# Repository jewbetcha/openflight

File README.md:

<p align="center">

  DIY Golf Launch Monitor using the OPS243-A Doppler Radar.
</p>

<p align="center">

</p>

> [!WARNING]
> **This project is in active development.** Features may be incomplete, unstable, or change without notice. Contributions and bug reports are welcome!

## Overview

OpenFlight is an open-source golf launch monitor built around the OPS243-A
Doppler radar, with an optional TI IWR6843 angle radar.

### What It Measures

- **Ball Speed**: 15-200 mph range with ±0.5% accuracy (OPS243-A)
- **Club Speed**: Detected from pre-impact readings (OPS243-A)
- **Smash Factor**: Ball speed / club speed ratio
- **Launch Angle**: Measured by the IWR6843; estimated when no trusted radar angle is available
- **Club Path**: Experimental pre-impact estimate from the IWR6843
- **Spin Rate**: Experimental candidate from rolling-buffer I/Q; not used for carry by default
- **Carry Distance**: Ballistic model with explicit fallbacks for missing measurements

### Hardware at a Glance

| Component | What it does | ~Cost |
|-----------|-------------|-------|
| OPS243-A Radar | Ball speed, club speed, experimental spin | $249 |
| Raspberry Pi 5 | Runs everything | $130 |
| 7" Touchscreen | Shows shot data | $46 |
| SparkFun SEN-14262 | Impact sound trigger for shot capture | $18 |
| Power supply + accessories | | $27 |
| **Subtotal, no angle radar** | | **~$400** |
| TI IWR6843LEVM + cable | Launch angle, experimental club path | $156 |
| **Total with angle radar** | | **~$556** |
| K-LD7 (×2) + FTDI adapters | Launch angle + club path (**deprecated**) | $140 |

Without an angle radar you still get ball speed, club speed, smash factor,
experimental spin, and estimated carry. The angle radar adds measured launch
angle and experimental club path.

> **⚠️ The K-LD7 angle radars are deprecated.** The supported angle radar is now the **TI IWR6843**. Don't buy K-LD7s for a new build; their software support remains for existing builds only. See the [full parts list](docs/PARTS.md) for details and links.

> **The IWR6843 needs custom firmware** — the stock TI demo doesn't expose the raw radar cube OpenFlight needs. A validated prebuilt image ships in `firmware/releases/`, so flashing it doesn't require the TI toolchain. See the [IWR6843 Operator Guide](docs/iwr6843/README.md).

## Getting Started

### 1. Get the parts

See the **[Parts List](docs/PARTS.md)** for everything you need with purchase links.

### 2. Wire it up

Follow the **[Sound Trigger Wiring Guide](docs/sound-trigger-wiring.md)** to connect the SEN-14262 to the OPS243-A. The (deprecated) K-LD7 modules connect via USB — no wiring needed.

**Adding the IWR6843 angle radar?** The Pi cannot power both radars over USB, so
the OPS243 moves to the Pi's GPIO UART header while the TI board takes the USB
port. Do it in this order, validating each step before the next — doing both at
once makes any failure ambiguous:

1. **[Move the OPS243 from USB to the Pi GPIO UART](docs/ops243-uart-migration.md)** — rewire and confirm the OPS still triggers on its own.
2. **[IWR6843 Operator Guide](docs/iwr6843/README.md)** — wire, flash the firmware, mount, aim, and measure geometry.

If your OPS243-A has **WiFi**, you cannot use the GPIO UART — its WiFi module
already drives the radar's UART receive line. Use a separately powered USB hub
instead; see the operator guide's Option B.

### 3. Set up the Pi

Flash Raspberry Pi OS (64-bit), plug in the radars, then run the interactive setup:

```bash
git clone https://github.com/jewbetcha/openflight.git
cd openflight
./scripts/setup/setup.sh
```

The script installs everything and walks you through the one-time hardware
configuration (radar flash setup, legacy K-LD7 device naming, auto-start, and
optional cloud sync) with prompts. It's safe to re-run any time.
See the **[Raspberry Pi Setup Guide](docs/raspberry-pi-setup.md)** for
details and troubleshooting. Touchscreen installations can use the
**[Startup Splash Screen](docs/splash-screen.md)** guide to install a
terminal-free desktop launcher with immediate startup progress.

### 4. Hit balls

```bash
# Default: rolling buffer mode with sound trigger
scripts/start-kiosk.sh

# With the IWR6843 angle radar (OPS243 on the Pi GPIO UART).
# Geometry values are examples — measure your own; see the operator guide.
scripts/start-kiosk.sh --iwr6843 \
  --ops-port /dev/ttyAMA0 \
  --iwr6843-tee-m 1.372 --iwr6843-net-m 4.064 \
  --iwr6843-tilt-deg 5.5 --iwr6843-radar-height-m 0.229 \
  --iwr6843-ball-height-m 0.021

# With legacy K-LD7 hardware (measure the mount tilt first)
scripts/start-kiosk.sh --kld7 --kld7-mount-tilt <measured-degrees>

# Swing speed training (air swings / speed sticks, no sound trigger)
scripts/start-kiosk.sh --swing-speed

# Development mode (no hardware)
scripts/start-kiosk.sh --mock

# With Geekworm X1202/X1206 battery monitoring
scripts/start-kiosk.sh --battery geekworm
```

The IWR6843 example values are not universal. Measure the geometry from the
antenna center and follow the [operator guide](docs/iwr6843/README.md#measure-the-geometry);
wrong values bias the result instead of producing an obvious startup error.

Then open http://localhost:8080 or use the touchscreen. Footer tabs switch
between Live, Stats, Shots, Camera, Players, and Debug. Tap the footer logo for
units, theme, and language; the footer power icon opens shutdown confirmation.
On Live, tap a metric to pin it top-left while keeping all metrics visible. Use
the Replay action on camera-backed shots to open a touch-friendly slow-motion
impact clip. The MP4 is generated only when Replay is selected and is cached
beside the raw camera capture. For a TV or tablet, use
[TV Display Mode](#tv-display-mode).

### 5. Sync to the cloud (optional)

OpenFlight can push your sessions to the **FlightWeb** cloud so you can review
shots from any device. It's opt-in, and **raw radar data never leaves your
Pi** — only shot results and session metadata are uploaded (verify with
`openflight-cloud push --dry-run`).

`setup.sh` offers to enable this and link your Pi. To do it by hand:

```bash
openflight-cloud link       # pair this Pi (enter a short code in your browser)
openflight-cloud status     # linked? queued? parked?
```

Once linked, sessions sync automatically (on session end and via a ~10-minute
timer that heals wifi outages). See the **[Cloud Sync Guide](docs/cloud-sync.md)**
for details.

### TV Display Mode

OpenFlight also serves a fullscreen-friendly browser display for tablets, TV browsers, or a Chrome tab cast to Chromecast.

1. Start OpenFlight as usual with `scripts/start-kiosk.sh`.
2. Find the OpenFlight host on your LAN — its hostname (see below) or its IP address.
3. Open `http://<openflight-host>:8080/display` from another laptop, tablet, or TV browser.
4. For Chromecast, open the display page in Chrome and use Chrome's built-in **Cast** feature to cast the tab.

> **Prefer the hostname over the IP.** Raspberry Pi OS broadcasts its hostname over
> mDNS (Avahi), so `http://openflight.local:8080/display` keeps working even when the
> Pi's DHCP lease expires and it comes back on a different address — a bookmarked IP
> breaks unless you reserved it on your router. Set the name in Raspberry Pi Imager's
> **Hostname** field when you flash the card; the default is `raspberrypi`, i.e.
> `raspberrypi.local`. The viewing device has to support mDNS — macOS, iOS, Windows 10+
> and most Linux desktops do, but some smart-TV browsers don't, so use the IP there.

This is browser/tab casting only. OpenFlight does not include native Cast SDK support yet.

### Swing Speed Training

For air swings and speed-stick training, OpenFlight can use the OPS243-A fast
speed stream directly instead of waiting for impact audio. Start it with
`scripts/start-kiosk.sh --swing-speed`; the server emits `swing_speed` events
with peak club speed, rep duration, reading count, and session stats. See the
**[Swing Speed Training Guide](docs/swing-speed-training.md)** for setup and
tuning options.

## How It Works

### System Architecture

```
SEN-14262 ── trigger ──► OPS243-A ── I/Q ──► RollingBufferMonitor
                                                   │
IWR6843 (optional) ── angle + club path ───────────┤
                                                   ▼
                                           Flask + WebSocket ──► React UI
```

1. **Sound trigger fires** — SEN-14262 detects club impact, triggers OPS243-A HOST_INT
2. **OPS243-A dumps buffer** — I/Q data is analyzed for ball speed, club speed, and an experimental spin candidate
3. **IWR6843 correlates** — The optional angle radar uses the same impact edge for launch angle and experimental club path
4. **Carry computed** — The ballistic model uses trusted measurements and fills missing inputs with documented fallbacks
5. **UI updates** — Shot data emitted via WebSocket to the React frontend

### Doppler Radar Basics

The OPS243-A transmits a 24 GHz signal. When it bounces off a moving object (the golf ball), the frequency shifts proportionally to the object's speed — this is the Doppler effect. At 24.125 GHz, each 1 mph of speed creates a ~71.7 Hz Doppler shift.

### Positioning

Place the OPS243-A **3-5 feet behind the tee**, pointing down the target line:

```
                Ball Flight Direction
                ======================>

[Tee]  ←--- 3-5 ft ---→  [OPS243-A]
```

The IWR6843 has stricter mounting and measurement requirements; use the
[operator guide](docs/iwr6843/README.md#mount-and-aim-the-radar) rather than assuming it
shares the OPS243 position.

## Configuration

### Radar Settings for Golf

| Setting        | Value                  | Why                                          |
| -------------- | ---------------------- | -------------------------------------------- |
| Mode           | Rolling buffer         | Raw I/Q capture for precise speeds and experimental spin |
| Sample Rate    | 30 ksps                | Supports up to ~208 mph ball speed           |
| Capture        | 4096 I/Q samples       | ~136 ms around impact                        |
| Trigger        | Sound (SEN-14262)      | ~10 µs hardware latency via HOST_INT         |
| Min Ball Speed | 15 mph                 | Minimum valid ball speed threshold (35 mph for speed-triggered mode) |
| DC Mask        | ~15 mph exclusion zone | Reject body movement and environmental noise |

These are applied automatically — the one-time flash configuration is handled
by the setup script.

### Python API

```python
from openflight.rolling_buffer import RollingBufferMonitor

monitor = RollingBufferMonitor()   # auto-detects the OPS243-A
monitor.connect()
monitor.start()

print("Swing when ready...")
shot = monitor.wait_for_shot(timeout=60)
if shot:
    print(f"Ball Speed: {shot.ball_speed_mph:.1f} mph")
    print(f"Est. Carry: {shot.estimated_carry_yards:.0f} yards")

monitor.stop()
monitor.disconnect()
```

## Limitations

- **Cosine error**: If ball doesn't travel directly toward/away from radar, measured speed will be slightly lower than actual
- **Spin detection**: The live multitaper value is experimental and is not used for carry by default. Short indoor flight windows and multipath make individual readings unreliable; see [Rolling Buffer and Spin Detection](docs/rolling_buffer_spin_detection.md).
- **K-LD7 speed aliasing** (deprecated hardware): The K-LD7 max speed is 62 mph, so it's used only for angle/distance, not speed

## Hardware Diagnostic

To verify the OPS243, sound trigger, and legacy K-LD7 path:

```bash
uv run python scripts/hardware-test/diagnose.py
```

The diagnostic checks the OPS243 transport, rolling-buffer persistence,
software and hardware triggers, and any connected K-LD7 radars. IWR6843 builds
use the [operator guide's first-capture checks](docs/iwr6843/README.md#verify-the-first-capture).

Missing optional hardware (like the horizontal K-LD7) is reported as a skip rather than a failure. Pass `--require-all` to fail on skips, or `--no-interactive` to skip the sound-trigger prompt in unattended runs.

## Project Structure

```
openflight/
├── src/openflight/
│   ├── ops243.py              # OPS243-A radar driver
│   ├── launch_monitor.py      # Shot detection & club/ball separation
│   ├── server.py              # Flask server and shot orchestration
│   ├── session_logger.py      # JSONL session logging
│   ├── rolling_buffer/        # OPS capture and signal processing
│   ├── iwr6843/               # Current angle radar
│   ├── kld7/                  # Legacy angle radar
│   ├── sim/                   # Simulator connector framework
│   └── cloud/                 # FlightWeb uploader
├── ui/                        # React frontend
├── scripts/                   # Utility & setup scripts
├── docs/                      # Documentation
└── pyproject.toml
```

## Community

Join the **[OpenFlight Discord](https://discord.gg/w8hhG4WVMN)** to ask build
questions, share results, and follow development.

## Contributing

Contributions welcome! See [CONTRIBUTING.md](CONTRIBUTING.md) for guidelines.

Areas of interest:

- **Better spin detection**: A dechirped Doppler-sideband estimator is in development (`scripts/analysis/replay_spin_dechirp.py`) — help validating it against launch-monitor truth data is especially welcome
- **Mobile app**: Bluetooth connection to phone

### Running Tests

```bash
uv run pytest tests/ -v
```

## Documentation

- **[Parts List](docs/PARTS.md)** — What to buy
- **[Sound Trigger Wiring](docs/sound-trigger-wiring.md)** — How to wire the sound trigger
- **[Raspberry Pi Setup](docs/raspberry-pi-setup.md)** — Full setup guide
- **[Electron Kiosk Shell](docs/electron-kiosk-shell.md)** — Why the kiosk runs in Electron and how self-updating could work later
- **[Battery Monitoring](docs/battery/README.md)** — Provider architecture, UI states, and shared Pi support
- **[Geekworm X1202/X1206 Operator Guide](docs/battery/geekworm.md)** — Batteries, Pi setup, native telemetry, and warnings
- **[IWR6843 Operator Guide](docs/iwr6843/README.md)** — Wire, flash, mount, aim, and calibrate the angle radar
- **[LIS3DH Inclinometer Setup](docs/inclinometer/README.md)**: Add enclosure-level compensation to IWR6843 tilt
- **[OPS243 USB → GPIO UART Migration](docs/ops243-uart-migration.md)** — Required before adding the IWR6843
- **[IWR6843 Firmware Developer Guide](firmware/README.md)** — Build the firmware from source (not needed to flash the prebuilt image)
- **[Simulator Connectors](docs/simulator/README.md)** — Stream shots to GSPro, OpenGolfSim, and others
- **[Cloud Sync](docs/cloud-sync.md)** — Push filtered sessions to FlightWeb
- **[Rolling Buffer & Spin Detection](docs/rolling_buffer_spin_detection.md)** — Production capture and experimental spin details
- **[Dechirped-Sideband Spin Replay](docs/spin-dechirp-replay.md)** — Next-gen spin estimator test bench
- **[Camera and YOLO Experiments](docs/yolo-performance-tuning.md)** — Optional, non-production vision work
- **[Legacy K-LD7 Setup](docs/kld7.md)** — Existing K-LD7 builds only
- **[K-LD7 Ball Detection Theory](docs/kld7-ball-detection-theory.md)** — How angle detection works (deprecated hardware)
- **[K-LD7 Session Review](docs/kld7-session-review.md)** — Offline review workflow for session JSONL files (deprecated hardware)
- **[Observability & Log Shipping](docs/observability.md)** — Ship logs to Grafana Cloud
- **[Contributing Guide](CONTRIBUTING.md)** — How to contribute
- **[Changelog](docs/CHANGELOG.md)** — Version history

## License

GNU Affero General Public License v3.0 or later (AGPL-3.0-or-later) - see LICENSE file.

## Acknowledgments

- [OmniPreSense](https://omnipresense.com/) for the OPS243-A radar and documentation
- The golf hacker community for inspiration

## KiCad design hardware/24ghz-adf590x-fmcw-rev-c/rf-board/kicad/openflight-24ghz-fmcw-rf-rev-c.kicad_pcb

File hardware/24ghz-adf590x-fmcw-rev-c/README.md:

# 24 GHz Active FMCW Radar — Rev C

This is an active FMCW two-board radar design for OpenFlight, replacing the Rev B2 passive RX array. It is authored natively in KiCad (the `generate_designs.mjs` pipeline is retired for Rev C).

**Specification:** [ADF590x Active FMCW Radar Rev C Design](../../docs/superpowers/specs/2026-07-01-adf590x-active-fmcw-rev-c-design.md)

## Status

- **Current:** In design, not ordered.
- **Validation:** KiCad ERC/DRC plus KiCad-skill analyzers certify design intent and fabricability.

## Band Plan

**TX 24.150–24.250 GHz, ≥25 MHz below/above nothing — OPS243 at 24.125 GHz stays outside the chirp band.**

The Rev C chirp occupies the upper ISM band with a 25 MHz guard band from the OPS243-A CW carrier, ensuring coexistence in both directions: Rev C's receiver is far outside the OPS's 50 kHz Doppler baseband, and OPS energy lands ≥25 MHz away in the Rev C baseband, well outside the ~100 kHz anti-alias corner.

## Design Boundaries

### RF Board (hybrid Rogers, ~70 × 50 mm)

- **RX array:** Four 2×2 patch subarrays in a 2×2 grid at ~1 lambda pitch (azimuth + elevation pair).
- **TX antenna:** Single series-fed 1×4 patch column (~10–11 dBi) on ADF5901 TX1, isolated from RX via stitched via fence.
- **Chipset:** ADF5901 (TX + LO), ADF5904 (4-channel RX), ADF4159 (PLL/ramp generator).
- **Stackup:** 4-layer hybrid, 10 mil RO4350B core (L1–L2), FR4 below. Impedance controlled: 50 Ω microstrip on L1 referenced to L2.

### ADC/Pi Interface Board (FR4)

- **ADC:** TLV320ADC3140 configured for 384 kHz capture in I2S/TDM mode (bit-exact, no resampling).
- **Anti-alias:** Scaling/filtering for ~100 kHz beat baseband; values reserved pending first measured ADF5904 levels.
- **Interface:** 2×15 SMD header (1.27 mm pitch) carrying 8 baseband channels (differential pairs), SPI control, power, and RAMP_SYNC GPIO.

## Directory Structure

```
hardware/24ghz-adf590x-fmcw-rev-c/
├── README.md (this file)
├── fabrication-notes.md
├── .gitignore
├── datasheets/
│   └── extracted/              # Extracted pages from ADI reference design docs
├── antenna/
│   └── results/                # HFSS EM sims + stackup verification report
├── library/
│   └── openflight-revc.pretty/ # KiCad footprint library
├── rf-board/
│   ├── kicad/                  # KiCad project and schematics
│   └── gerbers/                # Generated by kicad-cli (git-ignored)
└── adc-board/
    ├── kicad/                  # KiCad project and schematics
    └── gerbers/                # Generated by kicad-cli (git-ignored)
```

## Fabrication Gates

Before ordering PCB:

1. **Datasheet sync:** ADF5901, ADF5904, ADF4159, TLV320ADC3140 pin-level schematic verification against ADI reference design.
2. **PCBWay stackup confirmation in writing** (hybrid RO4350B core + FR4) with exact dielectric heights and Dk/Df before any antenna dimension is frozen.
3. **EM simulation:** HFSS patch calculations validated against the PCBWay-confirmed stackup.
4. **VNA coupon:** Panelized test coupon with main board for in-house impedance measurement.

## Bring-Up

1. Verify PCB assembly and probe SPI control lines to the ADI chips.
2. Configure ADF4159 in fixed CW mode at 24.200 GHz (no ramps) for initial Doppler and angle-of-arrival validation.
3. Enable FMCW mode once baseband levels and raw I2S capture are confirmed.

## Design Assumptions (Rev C Interim)

- Rogers RO4350B: 10 mil core, design Dk 3.66, Df 0.0037.
- **Any delta in the PCBWay-returned stackup table triggers re-running antenna and RF sims** (Tasks 5–8 in the project plan).

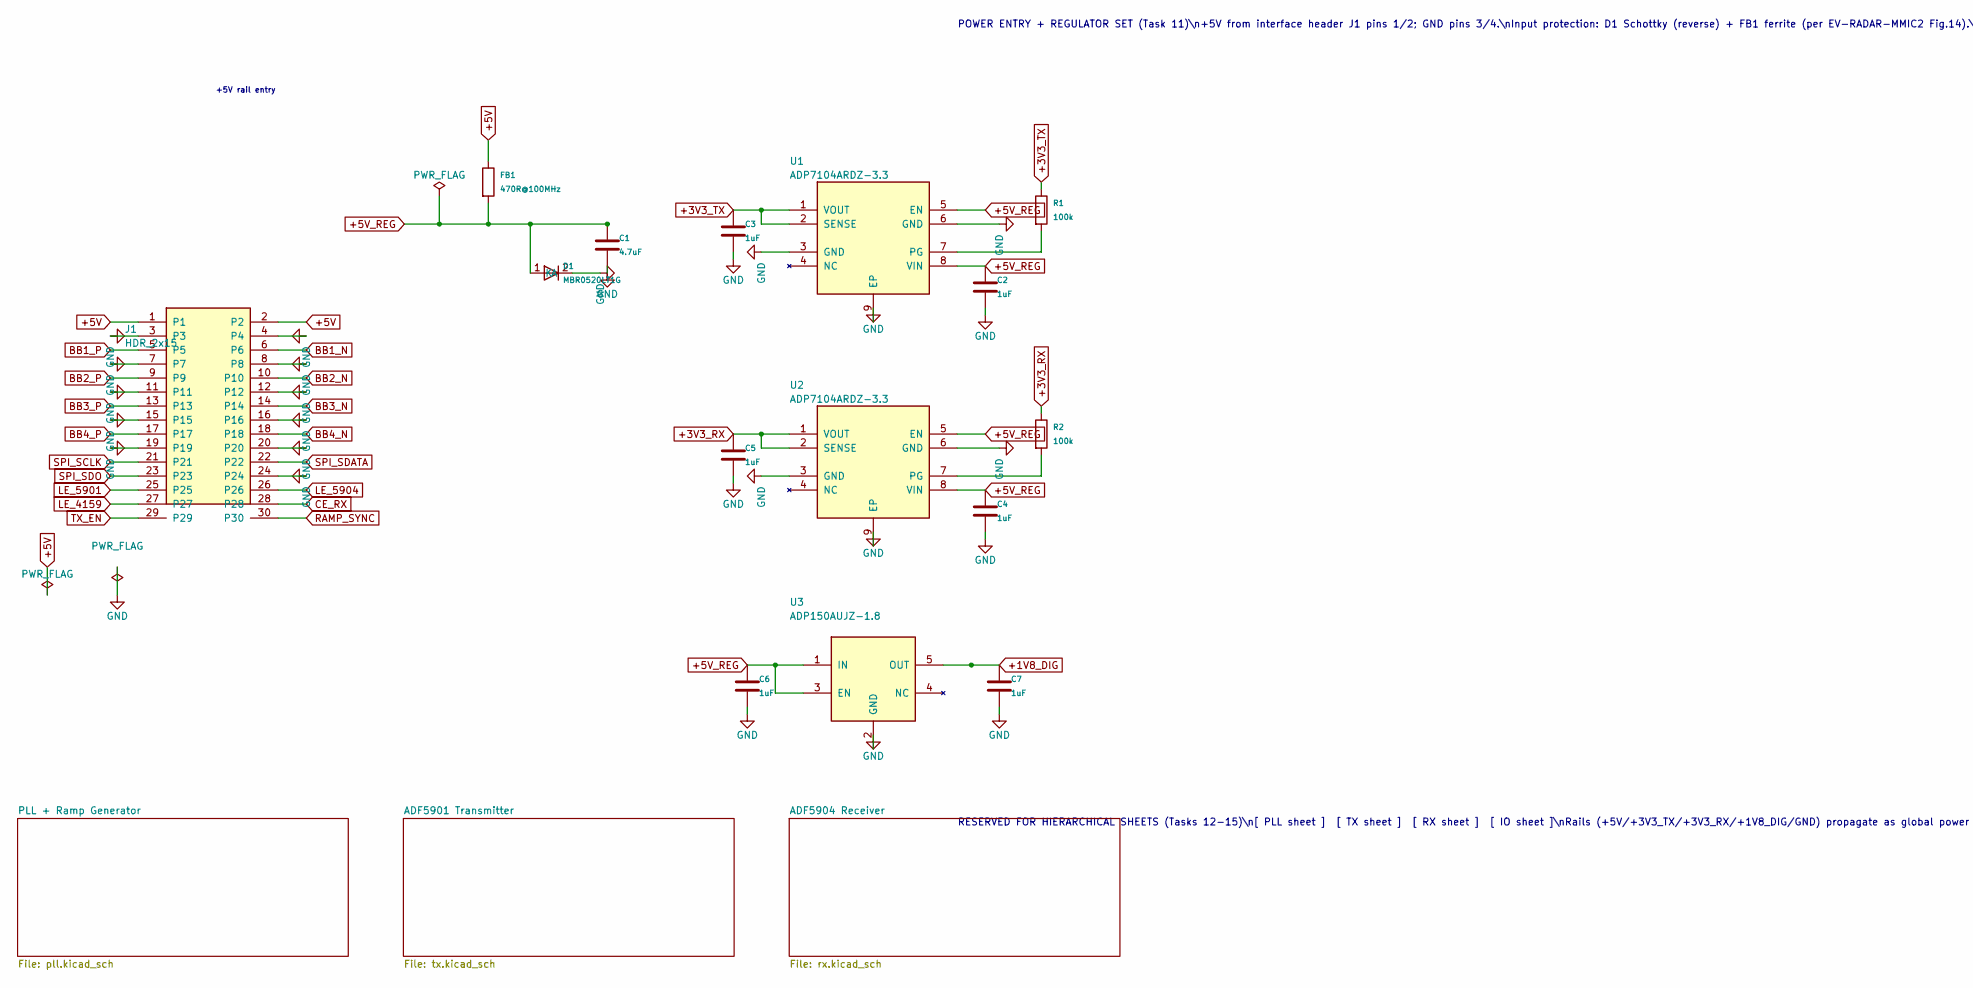
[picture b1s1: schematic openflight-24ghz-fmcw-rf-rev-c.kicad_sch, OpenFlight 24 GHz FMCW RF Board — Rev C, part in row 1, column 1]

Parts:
C1: 4.7uF; C_0603_1608Metric
C2, C3, C4, C5, C6, C7: 1uF; C_0603_1608Metric
D1: MBR0520LT1G; D_SOD-123; MPN MBR0520LT1G
FB1: 470R@100MHz; L_0603_1608Metric; MPN 742792642
J1: HDR_2x15; HDR_2x15_1.27MM_SMD; MPN FTSH-115-01-L-DV-K
R1, R2: 100k; R_0402_1005Metric
U1, U2: ADP7104ARDZ-3.3; ADP7104_SOIC8_EP; MPN ADP7104ARDZ-3.3
U3: ADP150AUJZ-1.8; ADP150_TSOT23_5; MPN ADP150AUJZ-1.8

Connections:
+1V8_DIG: C7.1, U3.5 (OUT); also elsewhere on the board
+3V3_RX: C5.1, R2.1, U2.1 (VOUT), U2.2 (SENSE); also elsewhere on the board
+3V3_TX: C3.1, R1.1, U1.1 (VOUT), U1.2 (SENSE); also elsewhere on the board
+5V: FB1.1, J1.1, J1.2; also elsewhere on the board
+5V_REG: C1.1, C2.1, C4.1, C6.1, D1.1 (K), FB1.2, U1.5 (EN), U1.8 (VIN), U2.5 (EN), U2.8 (VIN), U3.1 (IN), U3.3 (EN)
CE_RX: J1.28; also elsewhere on the board
LE_4159: J1.27; also elsewhere on the board
LE_5901: J1.25; also elsewhere on the board
LE_5904: J1.26; also elsewhere on the board
unnamed: R1.2, U1.7 (PG)
unnamed: R2.2, U2.7 (PG)
RAMP_SYNC: J1.30; also elsewhere on the board
SPI_SCLK: J1.21; also elsewhere on the board
SPI_SDATA: J1.22; also elsewhere on the board
SPI_SDO: J1.23; also elsewhere on the board
TX_EN: J1.29; also elsewhere on the board

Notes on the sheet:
POWER ENTRY + REGULATOR SET (Task 11)\n+5V from interface header J1 pins 1/2; GND pins 3/4.\nInput protection: D1 Schottky (reverse) + FB1 ferrite (per EV-RADAR-MMIC2 Fig.14).\nU1 ADP7104-3.3 -> +3V3_TX (ADF5901). U2 ADP7104-3.3 -> +3V3_RX (ADF5904 + ADF4159 analog).\nU3 ADP150-1.8 -> +1V8_DIG (ADF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
RESERVED FOR HIERARCHICAL SHEETS (Tasks 12-15)\n[ PLL sheet ] [ TX sheet ] [ RX sheet ] [ IO sheet ]\nRails (+5V/+3V3_TX/+3V3_RX/+1V8_DIG/GND) propagate as global power symbols;\nsignals cross via hierarchical pins added by those tasks.
+5V rail entry

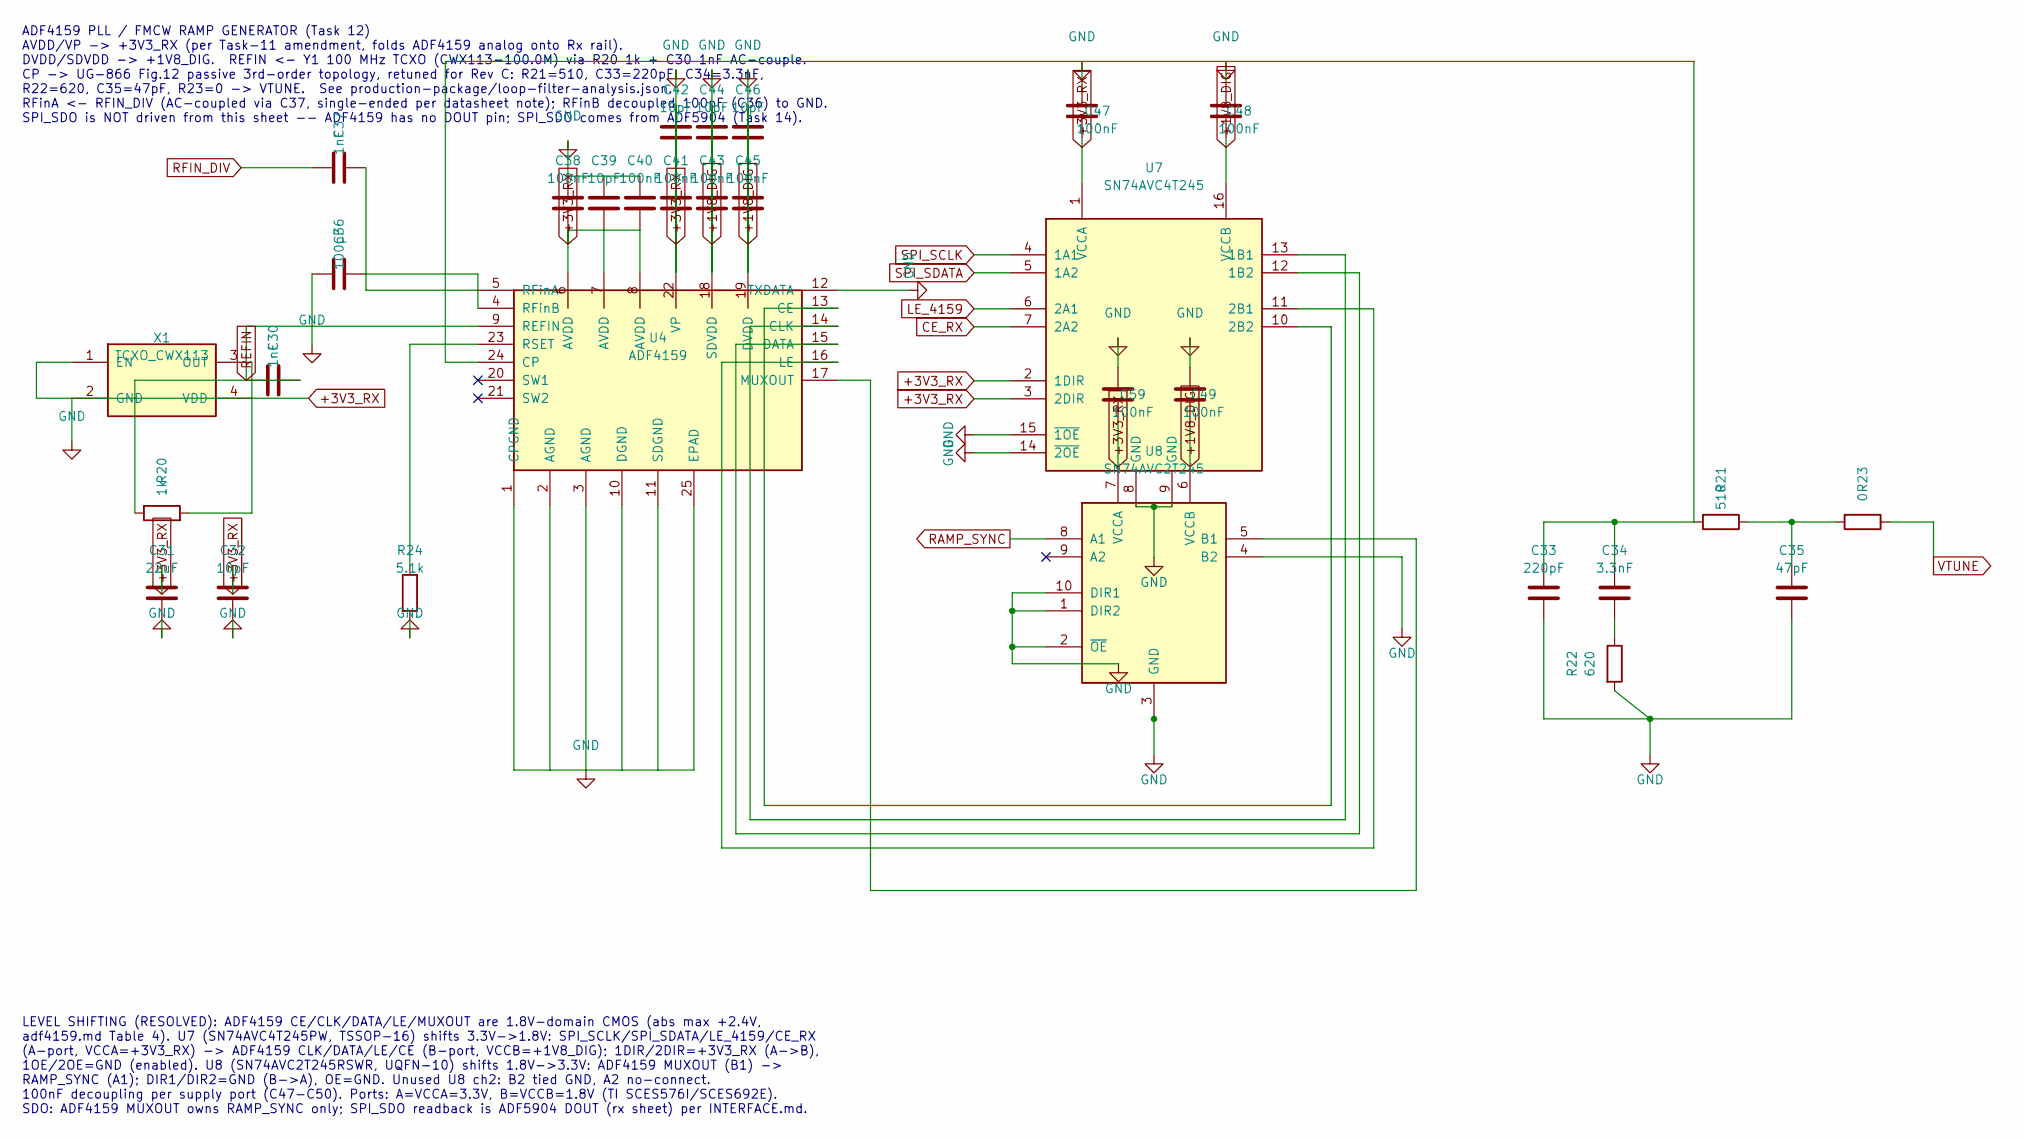
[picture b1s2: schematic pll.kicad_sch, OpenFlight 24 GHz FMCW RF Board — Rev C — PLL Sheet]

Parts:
C30, C37: 1nF; C_0402_1005Metric
C31: 22uF; C_0805_2012Metric
C32, C39, C42, C44, C46: 10pF; C_0402_1005Metric
C33: 220pF; C_0402_1005Metric
C34: 3.3nF; C_0402_1005Metric
C35: 47pF; C_0402_1005Metric
C36: 100pF; C_0402_1005Metric
C38, C40, C41, C43, C45, C47, C48, C49, C59: 100nF; C_0402_1005Metric
R20: 1k; R_0402_1005Metric
R21: 510; R_0402_1005Metric
R22: 620; R_0402_1005Metric
R23: 0; R_0402_1005Metric
R24: 5.1k; R_0402_1005Metric
U4: ADF4159; ADF4159_LFCSP24; MPN ADF4159CCPZ
U7: SN74AVC4T245; TSSOP-16_4.4x5mm_P0.65mm; MPN SN74AVC4T245PW
U8: SN74AVC2T245; Texas_RSW0010A_UQFN-10_1.4x1.8mm_P0.4mm; MPN SN74AVC2T245RSWR
X1: TCXO_CWX113; TCXO_CWX113_SMD4; MPN CWX113-100.0M

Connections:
+1V8_DIG: C43.2, C44.2, C45.2, C46.2, C48.2, C49.2, U4.18 (SDVDD), U4.19 (DVDD), U7.16 (VCCB), U8.6 (VCCB); also elsewhere on the board
+3V3_RX: C31.1, C32.1, C38.2, C39.2, C40.2, C41.2, C42.2, C47.2, C59.2, U4.6 (AVDD), U4.7 (AVDD), U4.8 (AVDD), U4.22 (VP), U7.1 (VCCA), U7.2 (1DIR), U7.3 (2DIR), U8.7 (VCCA), X1.1 (EN), X1.4 (VDD); also elsewhere on the board
CE_RX: U7.7 (2A2); also elsewhere on the board
LE_4159: U7.6 (2A1); also elsewhere on the board
unnamed: C30.2, R20.1
unnamed: C34.2, R22.1
unnamed: C35.1, R21.1, R23.2
unnamed: U4.13 (CE), U7.10 (2B2)
unnamed: U4.14 (CLK), U7.13 (1B1)
unnamed: U4.15 (DATA), U7.12 (1B2)
unnamed: U4.16 (LE), U7.11 (2B1)
unnamed: U4.17 (MUXOUT), U8.5 (B1)
unnamed: C37.2, U4.5 (RFinA)
unnamed: C36.2, U4.4 (RFinB)
unnamed: R24.1, U4.23 (RSET)
unnamed: R20.2, X1.3 (OUT)
RAMP_SYNC: U8.8 (A1); also elsewhere on the board
REFIN: C30.1, U4.9 (REFIN); also elsewhere on the board
RFIN_DIV: C37.1; also elsewhere on the board
SPI_SCLK: U7.4 (1A1); also elsewhere on the board
SPI_SDATA: U7.5 (1A2); also elsewhere on the board
VTUNE: R23.1; also elsewhere on the board

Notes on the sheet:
ADF4159 PLL / FMCW RAMP GENERATOR (Task 12) AVDD/VP -> +3V3_RX (per Task-11 amendment, folds ADF4159 analog onto Rx rail). DVDD/SDVDD -> +1V8_DIG. REFIN <- Y1 100 MHz TCXO (CWX113-100.0M) via R20 1k + C30 1nF AC-couple. CP -> UG-866 Fig.12 passive 3rd-order topology, retuned for Rev C: R21=510, C33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
LEVEL SHIFTING (RESOLVED): ADF4159 CE/CLK/DATA/LE/MUXOUT are 1.8V-domain CMOS (abs max +2.4V, adf4159.md Table 4). U7 (SN74AVC4T245PW, TSSOP-16) shifts 3.3V->1.8V: SPI_SCLK/SPI_SDATA/LE_4159/CE_RX (A-port, VCCA=+3V3_RX) -> ADF4159 CLK/DATA/LE/CE (B-port, VCCB=+1V8_DIG); 1DIR/2DIR=+3V3_RX (A->B), 1O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

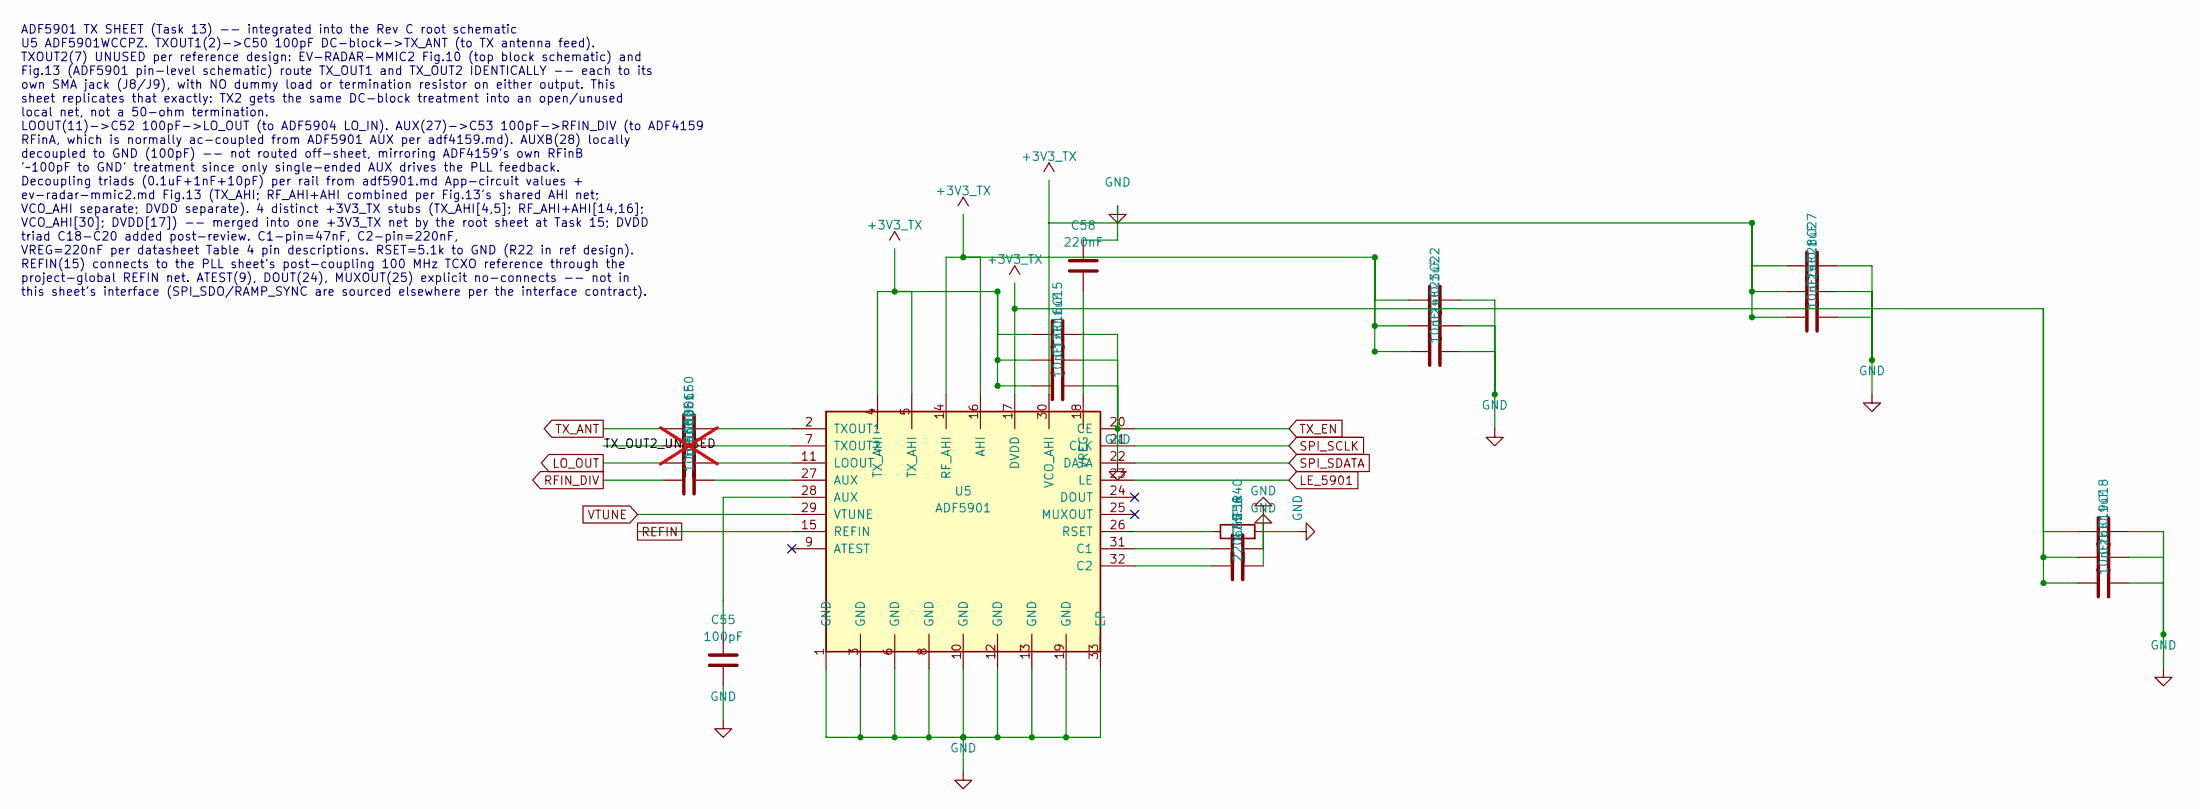
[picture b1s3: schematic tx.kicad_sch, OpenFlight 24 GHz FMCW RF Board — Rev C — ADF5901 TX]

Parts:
C15, C18, C22, C27: 0.1uF; C_0402_1005Metric
C16, C19, C23, C28: 1nF; C_0402_1005Metric
C17, C20, C24, C29: 10pF; C_0402_1005Metric
C50, C52: 100nF; C_0402_1005Metric; MPN 550L104KTT
C51: 100pF; C_0402_1005Metric; not fitted
C53: 10pF; C_0201_0603Metric; MPN 0201ZK100FBSTR
C55: 100pF; C_0402_1005Metric
C56: 47nF; C_0402_1005Metric
C57, C58: 220nF; C_0402_1005Metric
R40: 5.1k; R_0402_1005Metric
U5: ADF5901; ADF5901_LFCSP32; MPN ADF5901WCCPZ

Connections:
+3V3_TX: C15.1, C16.1, C17.1, C18.1, C19.1, C20.1, C22.1, C23.1, C24.1, C27.1, C28.1, C29.1, U5.4 (TX_AHI), U5.5 (TX_AHI), U5.14 (RF_AHI), U5.16 (AHI), U5.17 (DVDD), U5.30 (VCO_AHI); also elsewhere on the board
/ADF5901 Transmitter/TX_OUT2_UNUSED: C51.1
LE_5901: U5.23 (LE); also elsewhere on the board
LO_OUT: C52.1; also elsewhere on the board
unnamed: C53.2, U5.27 (AUX)
unnamed: C55.1, U5.28 (AUX)
unnamed: C56.1, U5.31 (C1)
unnamed: C57.1, U5.32 (C2)
unnamed: C52.2, U5.11 (LOOUT)
unnamed: R40.1, U5.26 (RSET)
unnamed: C50.2, U5.2 (TXOUT1)
unnamed: C51.2, U5.7 (TXOUT2)
unnamed: C58.2, U5.18 (VREG)
REFIN: U5.15 (REFIN); also elsewhere on the board
RFIN_DIV: C53.1; also elsewhere on the board
SPI_SCLK: U5.21 (CLK); also elsewhere on the board
SPI_SDATA: U5.22 (DATA); also elsewhere on the board
TX_ANT: C50.1; also elsewhere on the board
TX_EN: U5.20 (CE); also elsewhere on the board
VTUNE: U5.29 (VTUNE); also elsewhere on the board

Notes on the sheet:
ADF5901 TX SHEET (Task 13) -- integrated into the Rev C root schematic U5 ADF5901WCCPZ. TXOUT1(2)->C50 100pF DC-block->TX_ANT (to TX antenna feed). TXOUT2(7) UNUSED per reference design: EV-RADAR-MMIC2 Fig.10 (top block schematic) and Fig.13 (ADF5901 pin-level schematic) route TX_OUT1 and TX_OUT2 I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

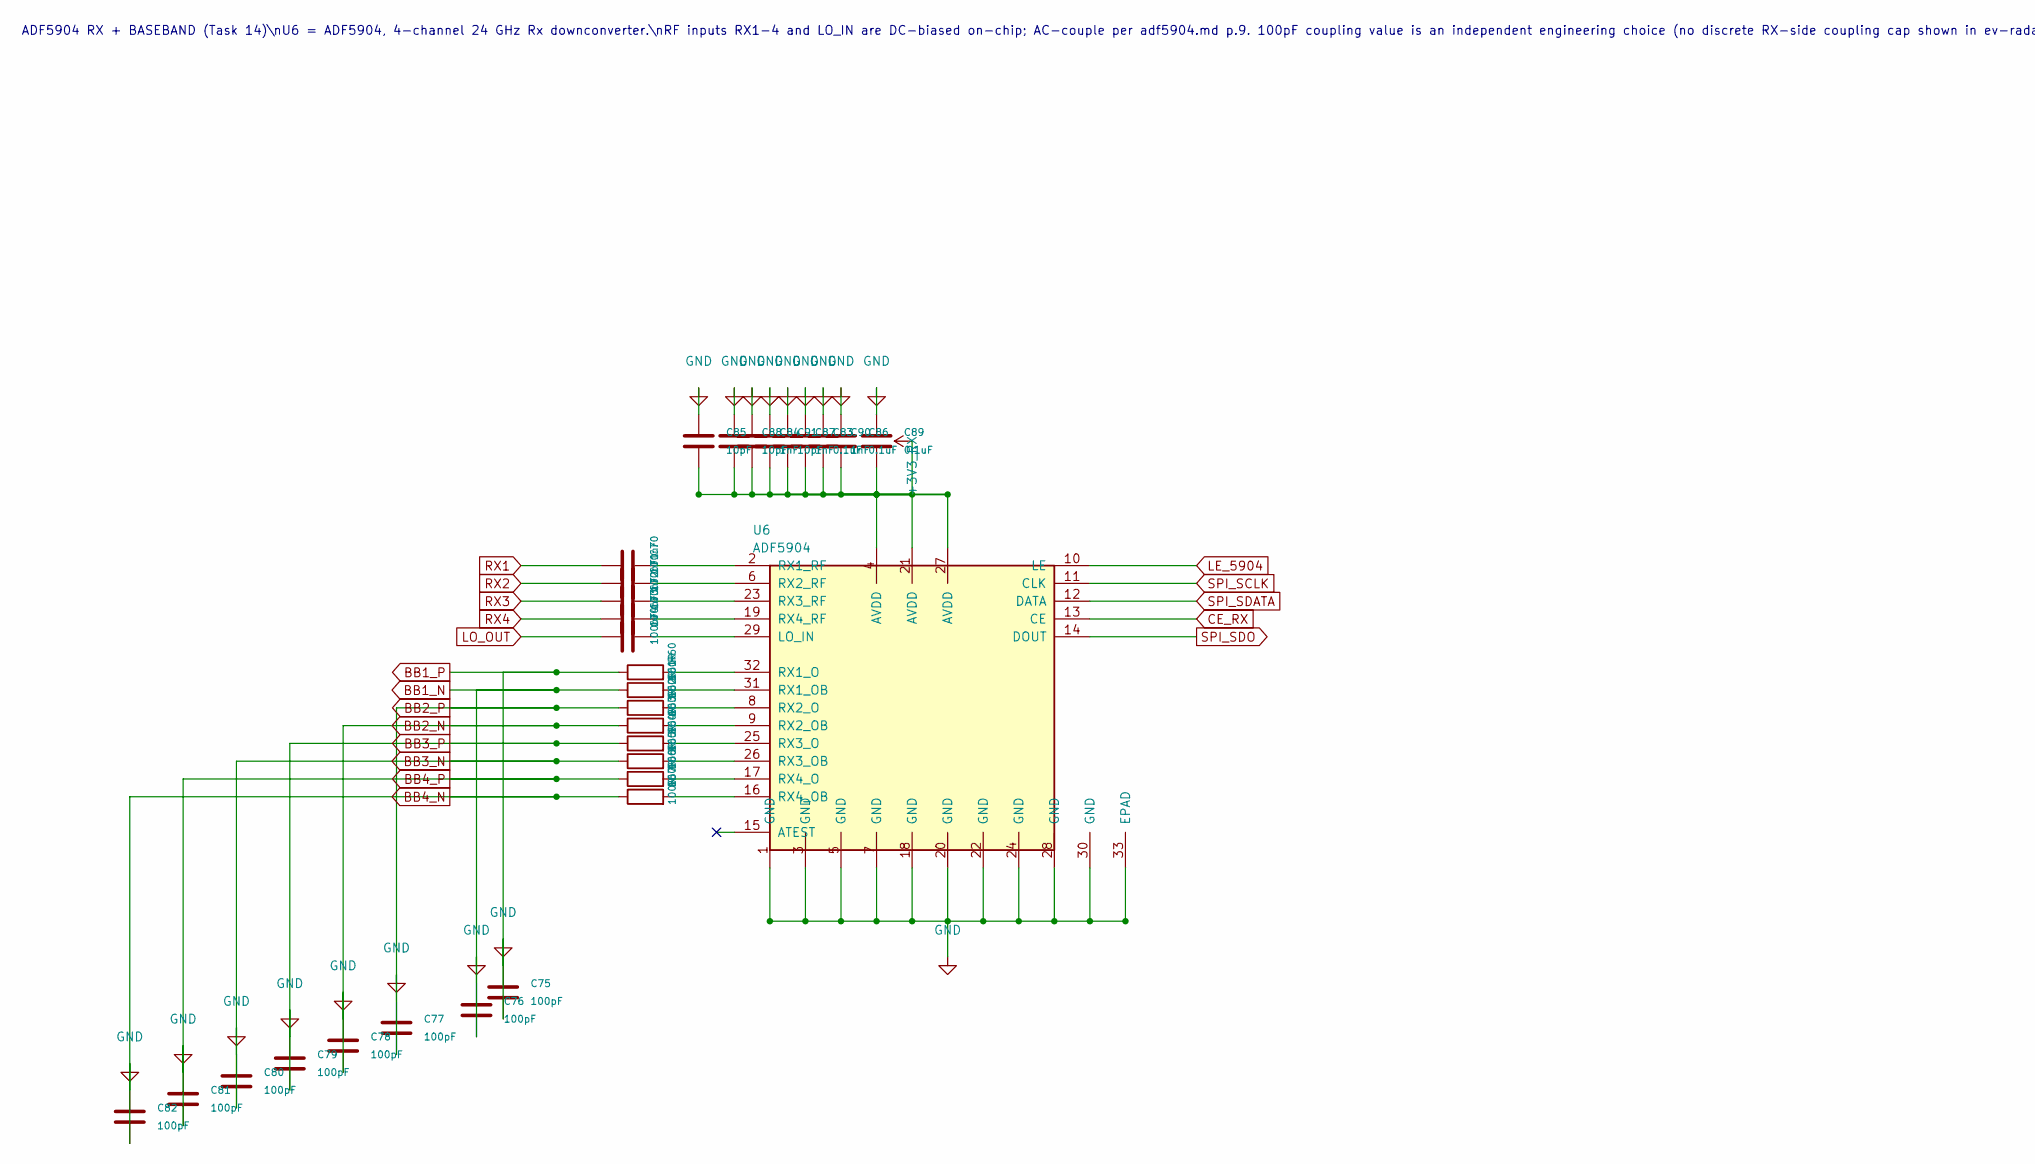
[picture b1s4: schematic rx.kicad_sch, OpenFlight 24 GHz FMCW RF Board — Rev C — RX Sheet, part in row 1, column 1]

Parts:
C70, C71, C72, C73, C74: 100nF; C_0402_1005Metric; MPN 550L104KTT
C75, C76, C77, C78, C79, C80, C81, C82: 100pF; C_0402_1005Metric
C83, C86, C89: 0.1uF; C_0402_1005Metric
C84, C87, C90: 1nF; C_0402_1005Metric
C85, C88, C91: 10pF; C_0402_1005Metric
R60, R61, R62, R63, R64, R65, R66, R67: 100R; R_0402_1005Metric
U6: ADF5904; ADF5904_LFCSP32; MPN ADF5904WCCPZ

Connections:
+3V3_RX: C83.2, C84.2, C85.2, C86.2, C87.2, C88.2, C89.2, C90.2, C91.2, U6.4 (AVDD), U6.21 (AVDD), U6.27 (AVDD); also elsewhere on the board
CE_RX: U6.13 (CE); also elsewhere on the board
LE_5904: U6.10 (LE); also elsewhere on the board
LO_OUT: C74.1; also elsewhere on the board
unnamed: C74.2, U6.29 (LO_IN)
unnamed: R60.2, U6.32 (RX1_O)
unnamed: R61.2, U6.31 (RX1_OB)
unnamed: C70.2, U6.2 (RX1_RF)
unnamed: R62.2, U6.8 (RX2_O)
unnamed: R63.2, U6.9 (RX2_OB)
unnamed: C71.2, U6.6 (RX2_RF)
unnamed: R64.2, U6.25 (RX3_O)
unnamed: R65.2, U6.26 (RX3_OB)
unnamed: C72.2, U6.23 (RX3_RF)
unnamed: R66.2, U6.17 (RX4_O)
unnamed: R67.2, U6.16 (RX4_OB)
unnamed: C73.2, U6.19 (RX4_RF)
RX1: C70.1; also elsewhere on the board
RX2: C71.1; also elsewhere on the board
RX3: C72.1; also elsewhere on the board
RX4: C73.1; also elsewhere on the board
SPI_SCLK: U6.11 (CLK); also elsewhere on the board
SPI_SDATA: U6.12 (DATA); also elsewhere on the board
SPI_SDO: U6.14 (DOUT); also elsewhere on the board

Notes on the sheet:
ADF5904 RX + BASEBAND (Task 14)\nU6 = ADF5904, 4-channel 24 GHz Rx downconverter.\nRF inputs RX1-4 and LO_IN are DC-biased on-chip; AC-couple per adf5904.md p.9. 100pF coupling value is an independent engineering choice (no discrete RX-side coupling cap shown in ev-radar-mmic2.md; Fig.23 there cove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

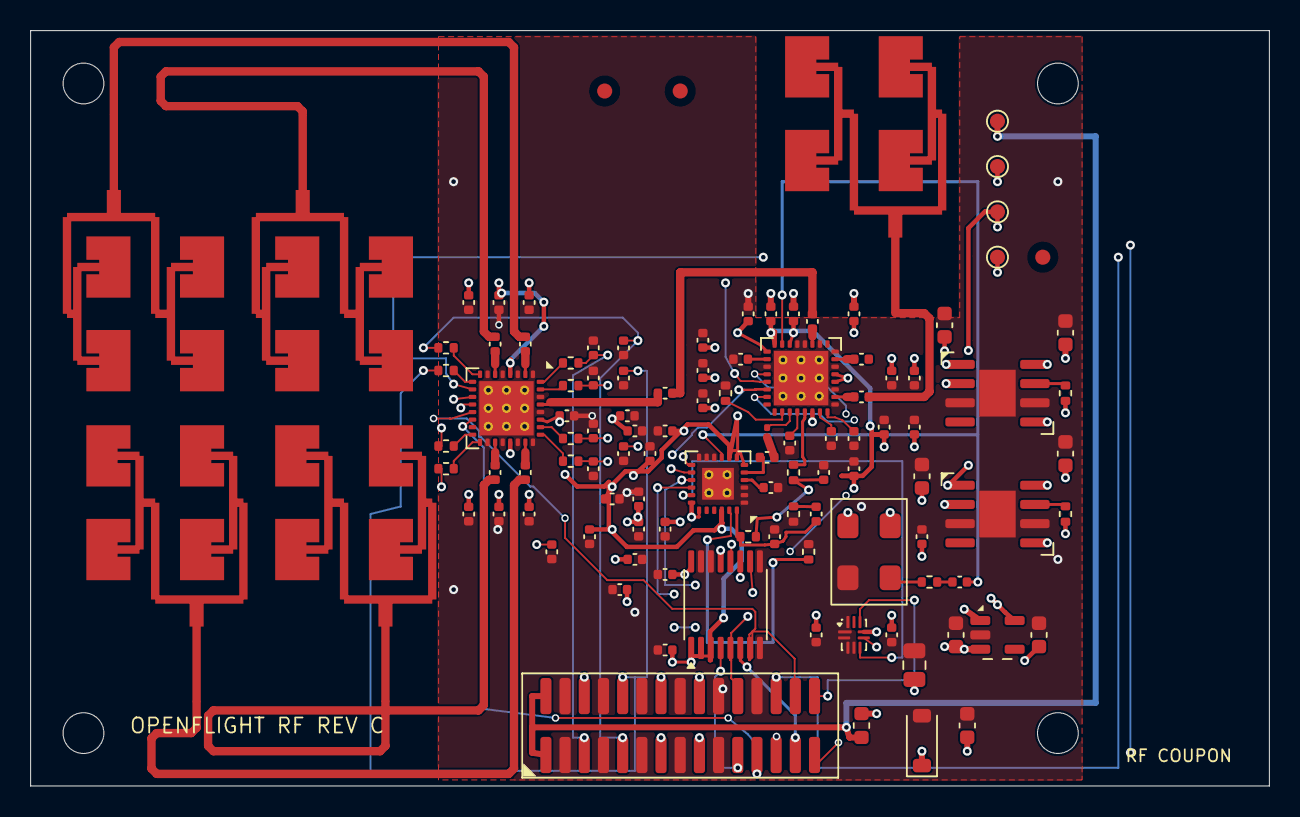
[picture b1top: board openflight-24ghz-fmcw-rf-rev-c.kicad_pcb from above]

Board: 4 copper layers, 82.0 x 50.0 mm, 114 parts (0 on the bottom side), 69 nets.

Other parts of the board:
ANT_RX1: RX1; RX_SUBARRAY_2X2
ANT_RX2: RX2; RX_SUBARRAY_2X2
ANT_RX3: RX3; RX_SUBARRAY_2X2
ANT_RX4: RX4; RX_SUBARRAY_2X2
ANT_TX1: TX_ANT; TX_ARRAY_2X2
FID1, FID2, FID3: Fiducial; Fiducial_1mm_Mask2mm
H1, H2, H3, H4: M2.5; MountingHole_2.7mm
TP1: +5V; TestPoint_Pad_D1.0mm
TP2: +3V3_TX; TestPoint_Pad_D1.0mm
TP3: +3V3_RX; TestPoint_Pad_D1.0mm
TP4: +1V8_DIG; TestPoint_Pad_D1.0mm

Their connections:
+1V8_DIG: TP4.1; also elsewhere on the board
+3V3_RX: TP3.1; also elsewhere on the board
+3V3_TX: TP2.1; also elsewhere on the board
+5V: TP1.1; also elsewhere on the board
RX1: ANT_RX1.1; also elsewhere on the board
RX2: ANT_RX2.1; also elsewhere on the board
RX3: ANT_RX3.1; also elsewhere on the board
RX4: ANT_RX4.1; also elsewhere on the board
TX_ANT: ANT_TX1.1; also elsewhere on the board
